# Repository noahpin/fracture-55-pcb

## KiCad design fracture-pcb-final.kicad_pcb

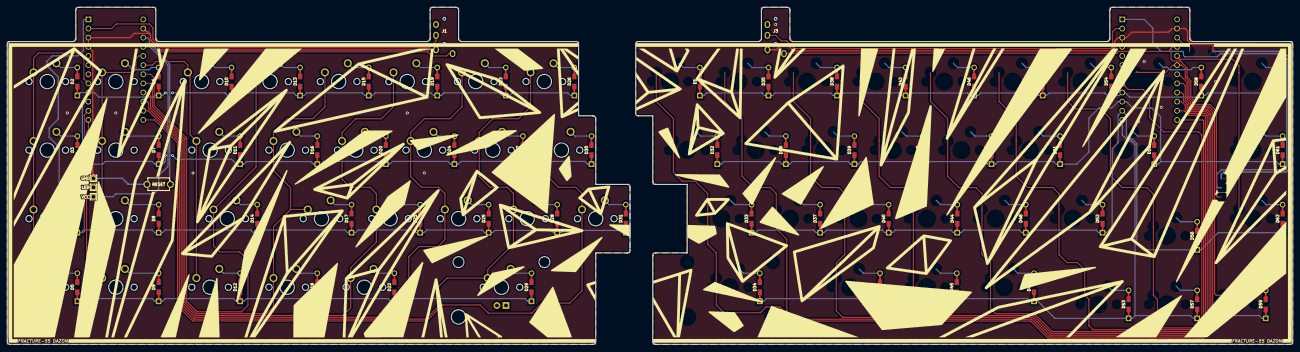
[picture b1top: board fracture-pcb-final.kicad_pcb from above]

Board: 2 copper layers, 357.2 x 93.7 mm, 99 parts (0 on the bottom side), 53 nets.

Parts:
D1, D2, D3, D4, D5, D6, D7, D8, D9, D10, D11, D12, D13, D14, D15, D16, D17, D18, D19, D20, D21, D22, D23, D24, D25, D26, D27, D28, D29, D30, D31, D32, D33, D34, D35, D36, D37, D38, D39, D40, D41, D42, D43, D44, D45, D46, D47, D48, D49, D50, D51, D52, D53, D54, D55, D56, D57, D58, D59, D60, D61, D62: D_Small; Diode-dual
J1, J3: MJ-4PP-9-Lily58-cache; TRRS-PJ-320A-BOTTOM
J2: Conn_01x03; LED
MX_: MXOnly-1U-NoLED
MX_A1: MX-NoLED; MXOnly-1U-NoLED
MX_ALT1: MX-NoLED; MXOnly-1.25U-NoLED
MX_B1: MX-NoLED; MXOnly-1U-NoLED
MX_C1: MX-NoLED; MXOnly-1U-NoLED
MX_CAPS1: MX-NoLED; MXOnly-1.25U-NoLED
MX_CODE1: MX-NoLED; MXOnly-1U-NoLED
MX_CTRL1: MX-NoLED; MXOnly-1.25U-NoLED
MX_D1: MX-NoLED; MXOnly-1U-NoLED
MX_E1: MX-NoLED; MXOnly-1U-NoLED
MX_ENTER1: MX-NoLED; MXOnly-2.75U
MX_F1: MX-NoLED; MXOnly-1U-NoLED
MX_G1: MX-NoLED; MXOnly-1U-NoLED
MX_MACRO_1, MX_MACRO_2, MX_MACRO_3, MX_MACRO_5, MX_MACRO_6, MX_MACRO_7, MX_MACRO_8: MX-NoLED; MXOnly-1U-NoLED
MX_MACRO_4: _MACRO_4; MXOnly-1U-NoLED
MX_Q1: MX-NoLED; MXOnly-1U-NoLED
MX_R1: MX-NoLED; MXOnly-1U-NoLED
MX_S1: MX-NoLED; MXOnly-1U-NoLED
MX_SHIFT1: MX-NoLED; MXOnly-1.75U-NoLED
MX_T1: MX-NoLED; MXOnly-1U-NoLED
MX_TAB1: MX-NoLED; MXOnly-1U-NoLED
MX_V1: MX-NoLED; MXOnly-1U-NoLED
MX_W1: MX-NoLED; MXOnly-1U-NoLED
MX_X1: MX-NoLED; MXOnly-1U-NoLED
MX_Z1: MX-NoLED; MXOnly-1U-NoLED
SW1: SW_RST; TACT_SWITCH_TVBP06
U1, U2: ProMicro

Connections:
COL0: MX_MACRO_1.1, MX_MACRO_3.1, MX_MACRO_5.1, MX_MACRO_7.1, U1.8
COL1: MX_MACRO_2.1, MX_MACRO_4.1, MX_MACRO_6.1, MX_MACRO_8.1, U1.20
COL2: MX_CAPS1.1, MX_CTRL1.1, MX_TAB1.1, U1.19
COL3: MX_Q1.1, MX_SHIFT1.1, U1.18
COL4: MX_A1.1, MX_CODE1.1, MX_W1.1, MX_Z1.1, U1.17
COL5: MX_ALT1.1, MX_E1.1, MX_S1.1, MX_X1.1, U1.16
COL6: MX_C1.1, MX_D1.1, MX_R1.1, U1.15
COL7: MX_ENTER1.1, MX_F1.1, MX_T1.1, MX_V1.1, U1.14
COL8: MX_B1.1, MX_G1.1, U1.13
DATA: J1.3, U1.2
DATA_R: J3.3, U2.2
GND: J1.2, J2.1, J3.2, SW1.1, U1.3, U1.4, U1.23, U2.3, U2.4, U2.23
LED: J2.2, U1.1
unnamed: D2.2, MX_MACRO_1.2
unnamed: D3.2, MX_MACRO_3.2
unnamed: D4.2, MX_MACRO_5.2
unnamed: D5.2, MX_MACRO_7.2
unnamed: D6.2, MX_MACRO_2.2
unnamed: D7.2, MX_MACRO_4.2
unnamed: D8.2, MX_MACRO_6.2
unnamed: D9.2, MX_MACRO_8.2
unnamed: D10.2, MX_TAB1.2
unnamed: D11.2, MX_CAPS1.2
unnamed: D12.2, MX_CTRL1.2
unnamed: D13.2, MX_Q1.2
unnamed: D14.2, MX_SHIFT1.2
unnamed: D15.2, MX_W1.2
unnamed: D16.2, MX_A1.2
unnamed: D17.2, MX_Z1.2
unnamed: D18.2, MX_CODE1.2
unnamed: D19.2, MX_E1.2
unnamed: D20.2, MX_S1.2
unnamed: D21.2, MX_X1.2
unnamed: D22.2, MX_ALT1.2
unnamed: D23.2, MX_R1.2
unnamed: D24.2, MX_D1.2
unnamed: D25.2, MX_C1.2
unnamed: D26.2, MX_T1.2
unnamed: D27.2, MX_F1.2
unnamed: D28.2, MX_V1.2
unnamed: D29.2, MX_ENTER1.2
unnamed: D30.2, MX_G1.2
unnamed: D31.2, MX_B1.2
RESET: SW1.2, U1.22
ROW0: D2.1, D6.1, D10.1, D13.1, D15.1, D19.1, D23.1, D26.1, U1.9
ROW1: D3.1, D7.1, D11.1, D16.1, D20.1, D24.1, D27.1, D30.1, U1.10
ROW2: D4.1, D8.1, D14.1, D17.1, D21.1, D25.1, D28.1, D31.1, U1.11
ROW3: D5.1, D9.1, D12.1, D18.1, D22.1, D29.1, U1.12
ROW_R_0: D1.1, D35.1, D38.1, D42.1, D46.1, D50.1, D54.1, D58.1, D60.1, U2.9
ROW_R_1: D32.1, D36.1, D39.1, D43.1, D47.1, D51.1, D55.1, D61.1, U2.10
ROW_R_2: D33.1, D37.1, D40.1, D44.1, D48.1, D52.1, D56.1, D62.1, U2.11
ROW_R_3: D34.1, D41.1, D45.1, D49.1, D53.1, D57.1, D59.1, U2.12
VCC: J1.1, J2.3, J3.1, U1.21, U2.21

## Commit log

2020-12-31 import pcb
